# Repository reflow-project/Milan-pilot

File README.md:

# Milan-pilot
Repository for the models and software developed for the Milan pilot

# License Note
From Reflow's Consortium Agreement, Art. 9.2.8:

`
Although each Party may release its Results under the AGPL3-license – see Section 9.8.1 -, each Party shall ensure that it will remain able to grant Access Rights for implementation (see Section 9.3) as well as for Exploitation on fair and Reasonable conditions (see Section 9.4.1) to its Results by applying the principles of dual licensing under terms and conditions which do not qualify as Controlled License Terms to prevent that any Result or Background of a Party requesting Access Rights shall be subject to the copyleft-effect of the AGPL.
`

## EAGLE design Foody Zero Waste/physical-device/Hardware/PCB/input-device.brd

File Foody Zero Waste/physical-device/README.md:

# Foody Zero Waste
## BOTTO IoT device

## Content

Software and Hardware of the **BOTTO** IoT device for the project Reflow.

### Hardware

The **datasheets** of all the electronic components can be found [here](https://github.com/reflow-project/Milan-pilot/tree/main/Foody%20Zero%20Waste/physical-device/Hardware/Components%20Datasheet/)

The source files of the **custom PCB** of BOTTO can be found [here](https://github.com/reflow-project/Milan-pilot/tree/main/Foody%20Zero%20Waste/physical-device/Hardware/PCB/)

### Software

The **firmware** of BOTTO device with configuration and installation instructions can be found [here](https://github.com/reflow-project/Milan-pilot/tree/main/Foody%20Zero%20Waste/physical-device/Software/)

## Acknowledge
Foody Zero Waste is part of a project that has received funding from the European Union's Horizon 2020 research and innovation programme under grant agreement number 820937.

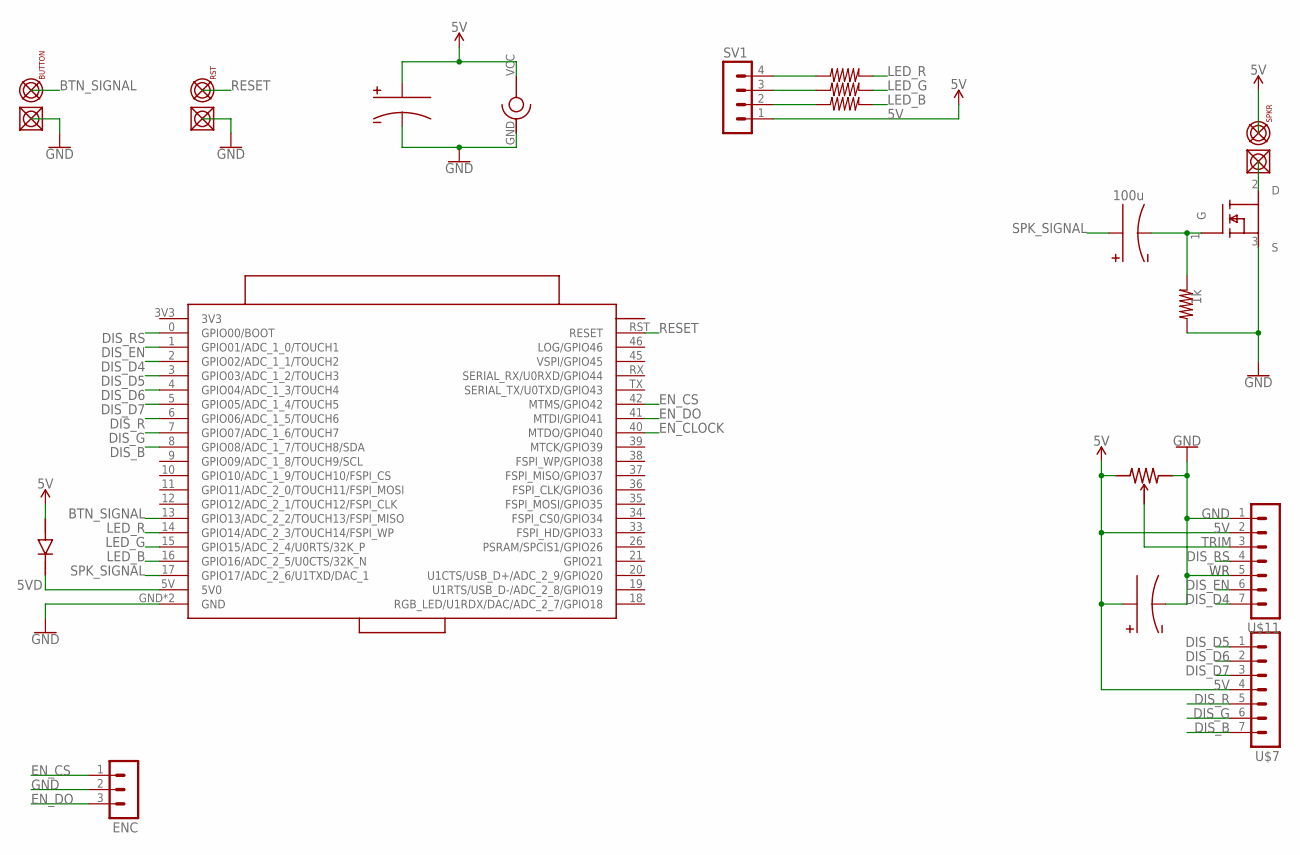
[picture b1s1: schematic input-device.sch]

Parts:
BUTTON: PIN-HEADER-02X1GROUND; 02X1-PAD-2.54PITCH-MASK-NAME
ENC: PIN-HEADER-03X1THRU-254; MA03-1
IRL540NPBF: MOSFET-N-IRL540NPBFBENDED-SHORTEST; TO220AH-SHORTEST-BEND
R: 1k; RESISTOR-THRU-1/4
RST: PIN-HEADER-02X1GROUND; 02X1-PAD-2.54PITCH-MASK-NAME
SPKR: PIN-HEADER-02X1GROUND; 02X1-PAD-2.54PITCH-MASK-NAME
SV1: PIN-HEADER-04X01; MA04-1
U$1, U$4: RESISTOR; RESISTOR-THRU-1/4
U$2: POWER-JACK; JACK-5.5X2.1-THRU
U$3: ESP32-S2-SAOLA-1
U$5: 100; RESISTOR-THRU-1/4
U$6, U$13: CAPACITOR-POLARIZEDCAP-DIAM-8.3MM-H-12MM-BENT; CAP-DIAM-8.3MM-H-12MM-BENT
U$7, U$11: PIN-HEADER-07X1; MA07-1
U$8: DIODE
U$9: TRIMMER; TRIMMER-PLASTIC-BLUE-9MM-2,54
U$14: 100u; CAP-DIAM-6.5MM-H-11.3MM-BENT-FLIP

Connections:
5V: SPKR.1, SV1.1, U$2.VCC, U$6.VCC, U$7.4, U$8.IN, U$9.A, U$11.2, U$13.VCC
5VD: U$3.5V (5V0), U$8.OUT
BTN_SIGNAL: BUTTON.1, U$3.13 (GPIO13/ADC_2_2/TOUCH13/FSPI_MISO)
DIS_B: U$3.8 (GPIO08/ADC_1_7/TOUCH8/SDA), U$7.7
DIS_D4: U$3.2 (GPIO02/ADC_1_1/TOUCH2), U$11.7
DIS_D5: U$3.3 (GPIO03/ADC_1_2/TOUCH3), U$7.1
DIS_D6: U$3.4 (GPIO04/ADC_1_3/TOUCH4), U$7.2
DIS_D7: U$3.5 (GPIO05/ADC_1_4/TOUCH5), U$7.3
DIS_EN: U$3.1 (GPIO01/ADC_1_0/TOUCH1), U$11.6
DIS_G: U$3.7 (GPIO07/ADC_1_6/TOUCH7), U$7.6
DIS_R: U$3.6 (GPIO06/ADC_1_5/TOUCH6), U$7.5
DIS_RS: U$3.0 (GPIO00/BOOT), U$11.4
EN_CLOCK: U$3.40 (MTDO/GPIO40)
EN_CS: ENC.1, U$3.42 (MTMS/GPIO42)
EN_DO: ENC.3, U$3.41 (MTDI/GPIO41)
GND: BUTTON.2, ENC.2, IRL540NPBF.3 (S), R.1, RST.2, U$2.GND, U$3.GND, U$3.GND2 (GND), U$6.GND, U$9.B, U$11.1, U$11.5, U$13.GND
LED_B: U$3.16 (GPIO16/ADC_2_5/U0CTS/32K_N), U$5.2
LED_B_RES: SV1.2, U$5.1
LED_G: U$3.15 (GPIO15/ADC_2_4/U0RTS/32K_P), U$4.2
LED_G_RES: SV1.3, U$4.1
LED_R: U$1.2, U$3.14 (GPIO14/ADC_2_3/TOUCH14/FSPI_WP)
LED_R_RES: SV1.4, U$1.1
unnamed: IRL540NPBF.1 (G), R.2, U$14.GND
RESET: RST.1, U$3.RST (RESET)
SPEAKER-SINK: IRL540NPBF.2 (D), SPKR.2
SPK_SIGNAL: U$3.17 (GPIO17/ADC_2_6/U1TXD/DAC_1), U$14.VCC
TRIM: U$9.C, U$11.3

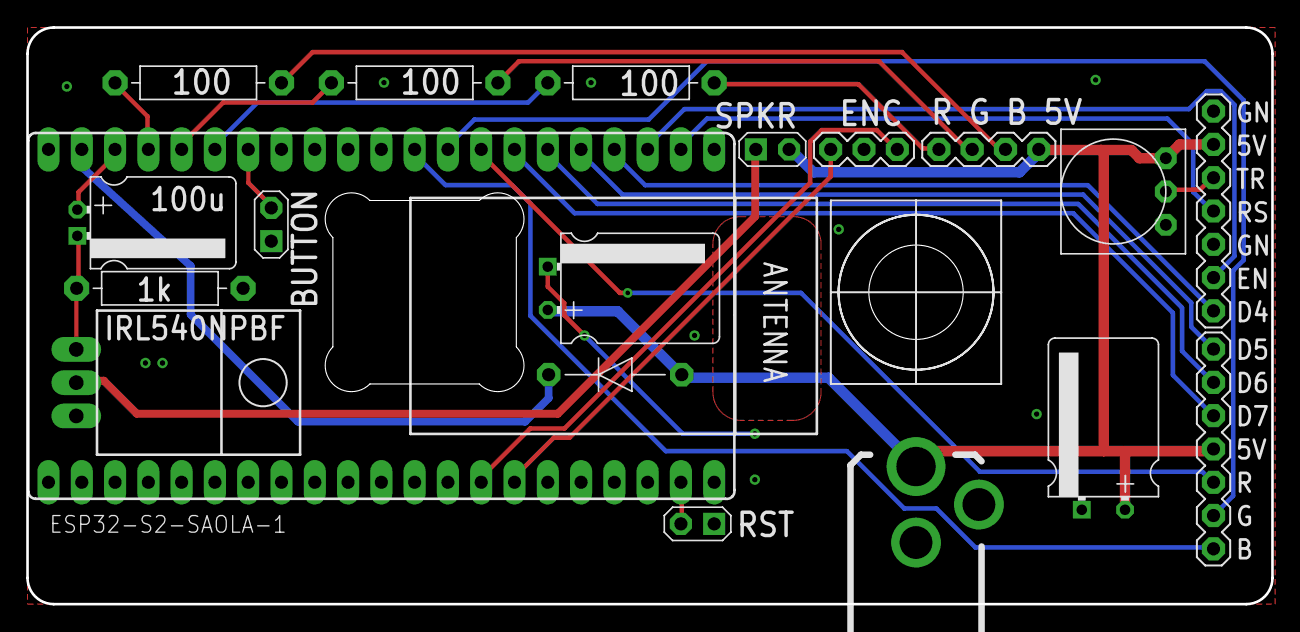
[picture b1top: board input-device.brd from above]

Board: 2 copper layers, 95.0 x 44.0 mm, 19 parts (0 on the bottom side), 26 nets.

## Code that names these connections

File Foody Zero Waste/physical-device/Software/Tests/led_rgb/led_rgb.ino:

#define LED_R 14
#define LED_G 15
#define LED_B 16

// PWM properties
const int freq = 5000;
const int RChannel = 0;
const int GChannel = 1;
const int BChannel = 2;
const int resolution = 8;

void setup() {
  Serial.begin(115200);
  ledcSetup(RChannel, freq, resolution);
  ledcSetup(GChannel, freq, resolution);
  ledcSetup(BChannel, freq, resolution);
  ledcAttachPin(LED_R, RChannel);
  ledcAttachPin(LED_G, GChannel);
  ledcAttachPin(LED_B, BChannel);  
}

void loop() {
  ledcWrite(RChannel, 0);
  ledcWrite(GChannel, 255);
  ledcWrite(BChannel, 255);  
  delay(1000);
  ledcWrite(RChannel, 255);
  ledcWrite(GChannel, 0);
  ledcWrite(BChannel, 255);  
  delay(1000);
  ledcWrite(RChannel, 255);
  ledcWrite(GChannel, 255);
  ledcWrite(BChannel, 0);   
  delay(1000);
}

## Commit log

2021-08-18 Create LICENSE
2021-11-12 initial commit - foody zero waste telegram bot
2021-11-12 pushed repository structure
2021-11-12 remove and revoke old bot token
2021-12-01 First commit of documentation
2021-12-01 remove unused file
2021-12-14 added 25% button to donations acceptance and implemented new offers reminder
2022-03-01 Production version added + architecture + db info
2022-03-02 folder
2022-03-03 telegram bot update
2022-03-03 included IoT device
2022-03-24 Adding Value Flows figures from D5.4
2022-03-24 Adding Value Flows figure from D5.4

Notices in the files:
parts and their libraries:
SparkFun-PowerSymbols: Licensing: Creative Commons ShareAlike 4.0 International - https://creativecommons.org/licenses/by-sa/4.0
